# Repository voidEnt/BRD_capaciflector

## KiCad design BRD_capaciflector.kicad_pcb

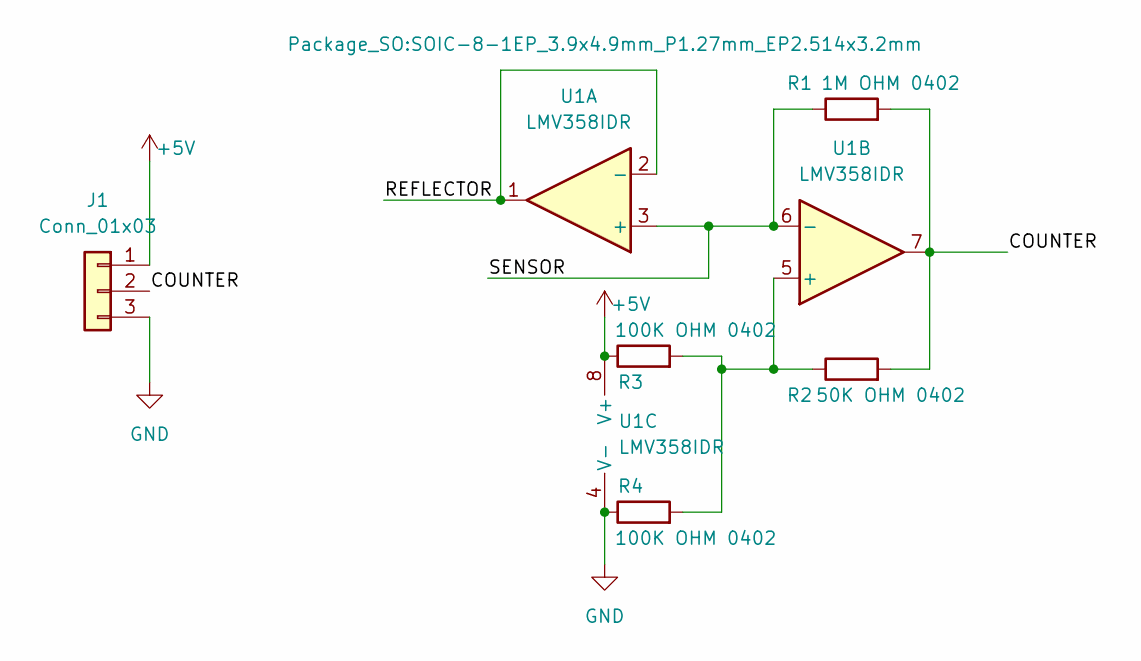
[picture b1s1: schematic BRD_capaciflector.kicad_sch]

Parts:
J1: Conn_01x03; PinHeader_1x03_P2.54mm_Horizontal
R1: 1M OHM 0402; R_0402_1005Metric
R2: 50K OHM 0402; R_0402_1005Metric
R3, R4: 100K OHM 0402; R_0402_1005Metric
U1: LMV358IDR; SOIC-8-1EP_3.9x4.9mm_P1.27mm_EP2.514x3.2mm

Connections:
+5V: J1.1, R3.1, U1.8 (V+)
/COUNTER: J1.2, R1.2, R2.2, U1.7
/REFLECTOR: U1.1, U1.2 (-)
/SENSOR: R1.1, U1.3 (+), U1.6 (-)
GND: J1.3, R4.1, U1.4 (V-)
unnamed: R2.1, R3.2, R4.2, U1.5 (+)

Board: 2 copper layers, 6 parts (0 on the bottom side), 6 nets, no tracks yet.
